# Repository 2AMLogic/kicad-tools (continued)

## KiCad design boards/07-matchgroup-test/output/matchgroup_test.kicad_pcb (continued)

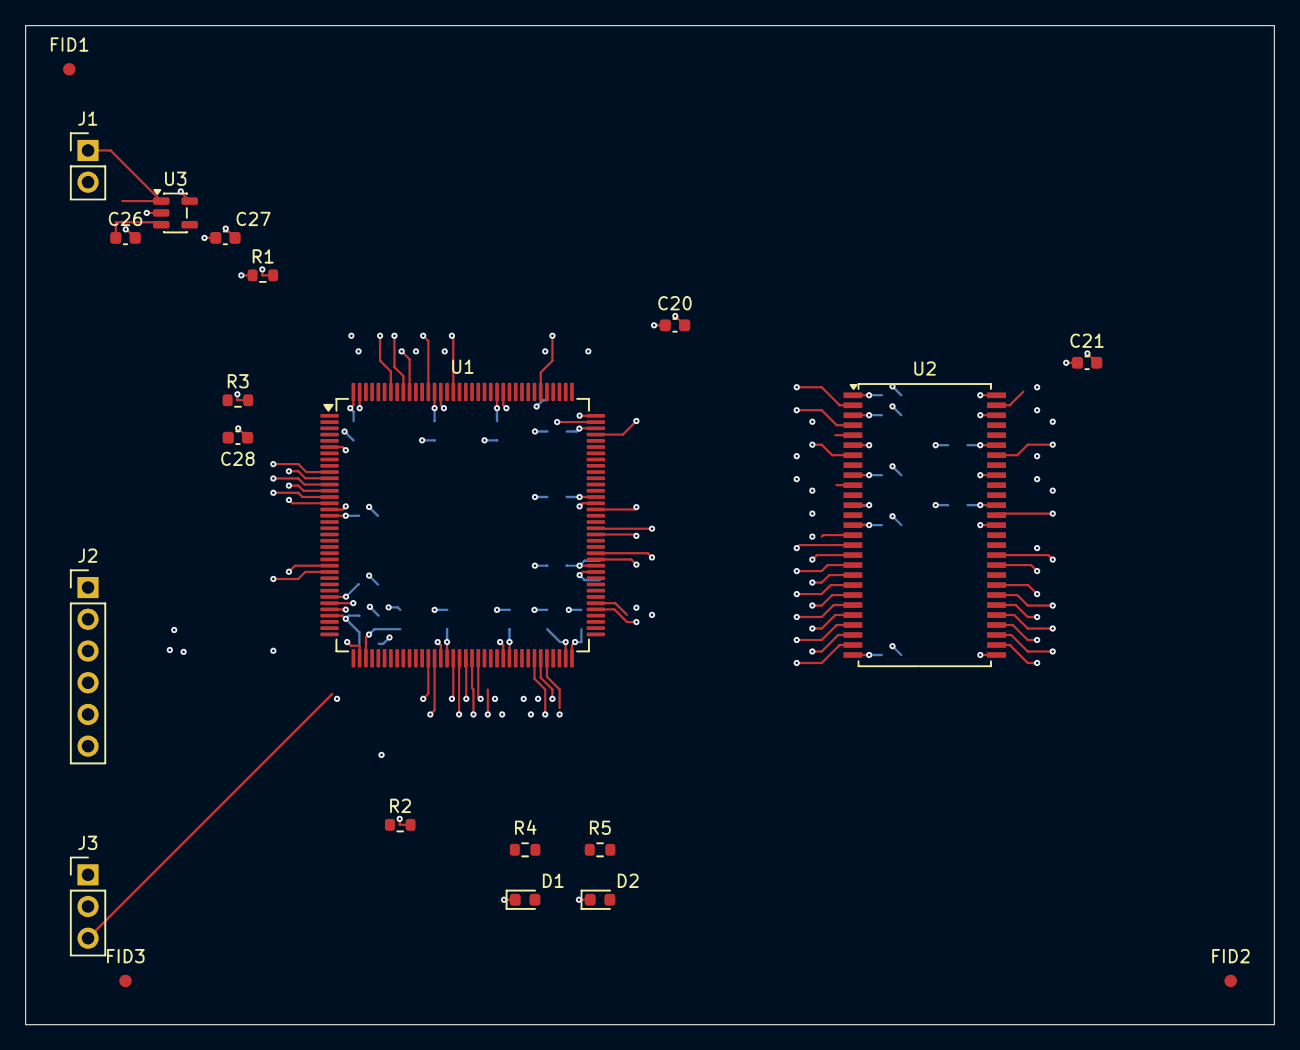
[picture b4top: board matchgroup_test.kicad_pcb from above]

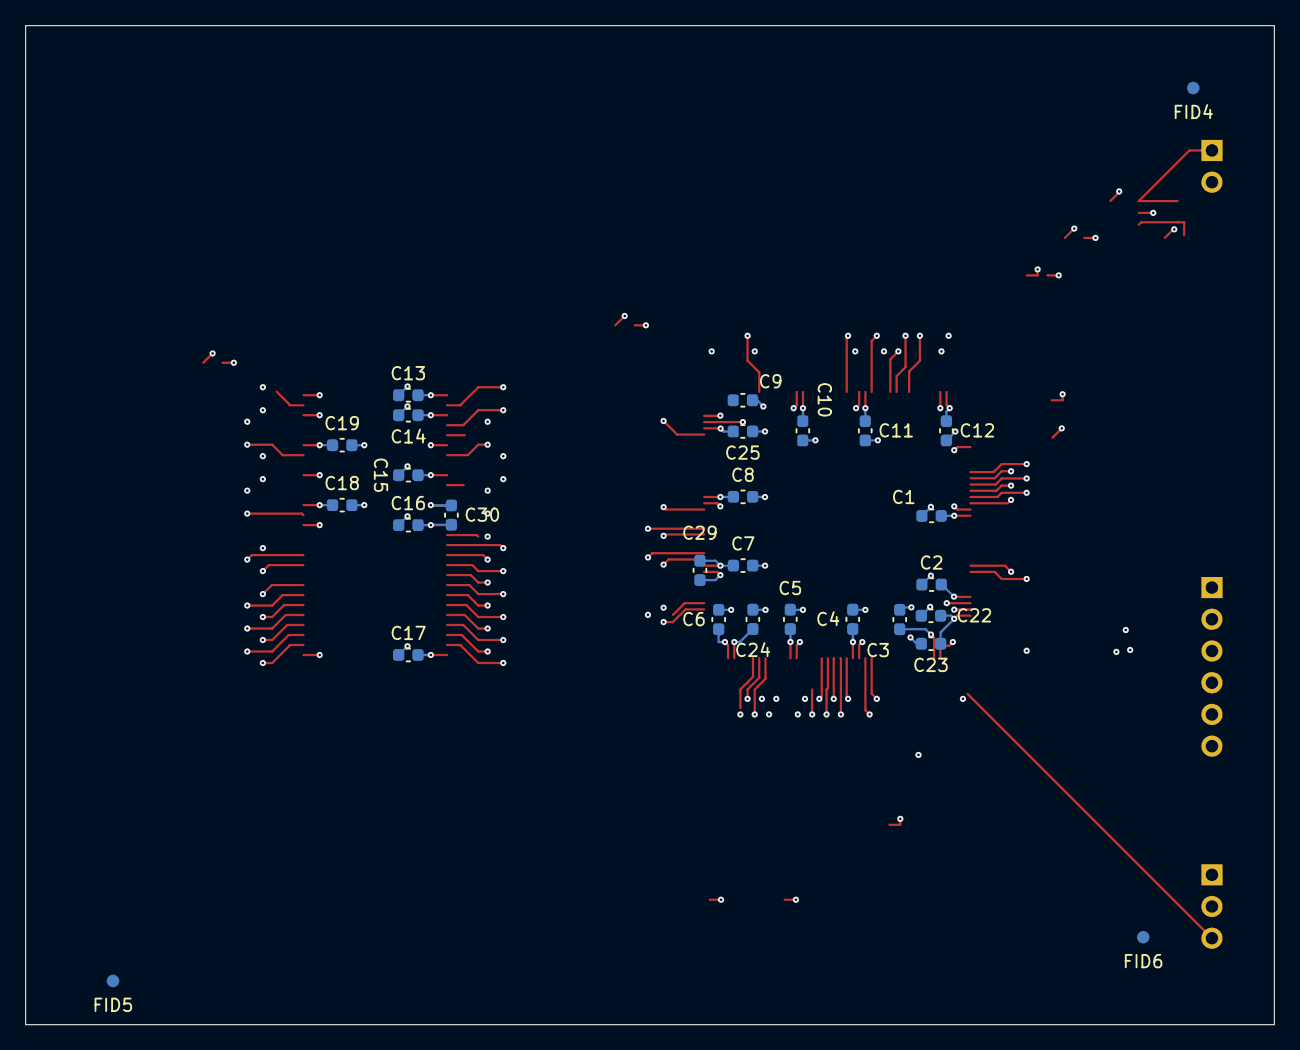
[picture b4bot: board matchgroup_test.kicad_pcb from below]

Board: 6 copper layers, 100.0 x 80.0 mm, 49 parts (28 on the bottom side), 55 nets.

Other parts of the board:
FID1, FID2, FID3, FID4, FID5, FID6: Fiducial; Fiducial_1mm_Mask2mm

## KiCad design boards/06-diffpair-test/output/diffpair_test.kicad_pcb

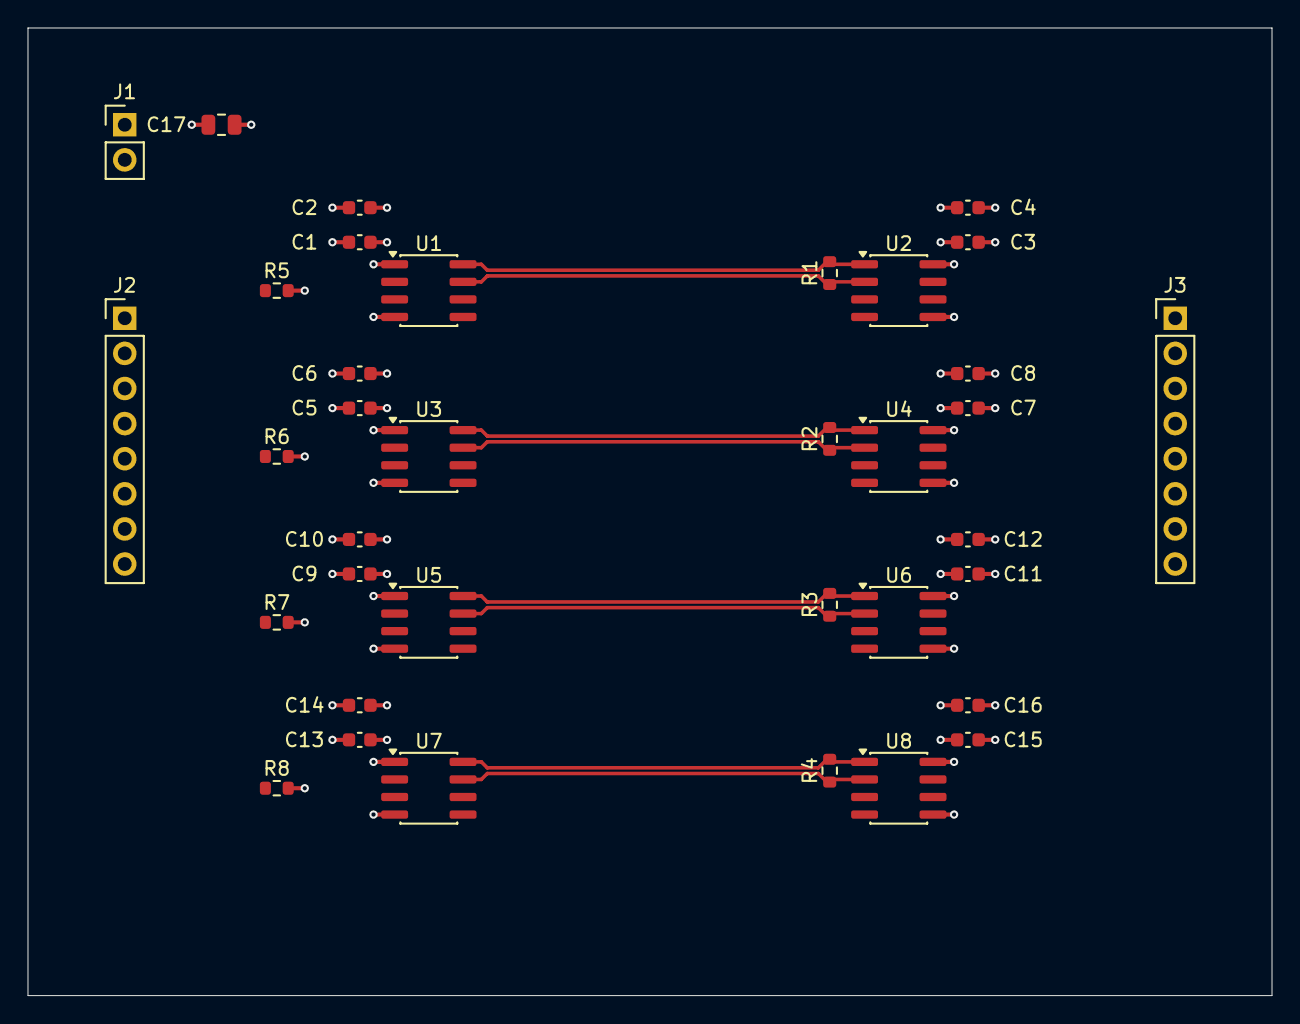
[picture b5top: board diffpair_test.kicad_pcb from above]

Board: 4 copper layers, 90.0 x 70.0 mm, 36 parts (0 on the bottom side), 18 nets.

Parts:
C1, C3, C5, C7, C9, C11, C13, C15: 1nF; C_0603_1608Metric
C2, C4, C6, C8, C10, C12, C14, C16: 100nF; C_0603_1608Metric
C17: 10uF; C_0805_2012Metric
J1: 3.3V regulated input; PinHeader_1x02_P2.54mm_Vertical
J2: IN1-4 / GND; PinHeader_1x08_P2.54mm_Vertical
J3: OUT1-4 / GND; PinHeader_1x08_P2.54mm_Vertical
R1, R2, R3, R4: 100; R_0603_1608Metric
R5, R6, R7, R8: 100k; R_0603_1608Metric
U1, U3, U5, U7: SN65LVDS1DR; SOIC-8_3.9x4.9mm_P1.27mm
U2, U4, U6, U8: SN65LVDS2DR; SOIC-8_3.9x4.9mm_P1.27mm

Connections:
+3V3: C1.1, C2.1, C3.1, C4.1, C5.1, C6.1, C7.1, C8.1, C9.1, C10.1, C11.1, C12.1, C13.1, C14.1, C15.1, C16.1, C17.1, J1.1, U1.1 (VCC), U2.8 (VCC), U3.1 (VCC), U4.8 (VCC), U5.1 (VCC), U6.8 (VCC), U7.1 (VCC), U8.8 (VCC)
GND: C1.2, C2.2, C3.2, C4.2, C5.2, C6.2, C7.2, C8.2, C9.2, C10.2, C11.2, C12.2, C13.2, C14.2, C15.2, C16.2, C17.2, J1.2, J2.2, J2.4, J2.6, J2.8, J3.2, J3.4, J3.6, J3.8, R5.2, R6.2, R7.2, R8.2, U1.4 (GND), U2.5 (GND), U3.4 (GND), U4.5 (GND), U5.4 (GND), U6.5 (GND), U7.4 (GND), U8.5 (GND)
IN1: J2.1, R5.1, U1.2 (D)
IN2: J2.3, R6.1, U3.2 (D)
IN3: J2.5, R7.1, U5.2 (D)
IN4: J2.7, R8.1, U7.2 (D)
LVDS1_N: R1.2, U1.8 (Z), U2.1 (B)
LVDS1_P: R1.1, U1.7 (Y), U2.2 (A)
LVDS2_N: R2.2, U3.8 (Z), U4.1 (B)
LVDS2_P: R2.1, U3.7 (Y), U4.2 (A)
LVDS3_N: R3.2, U5.8 (Z), U6.1 (B)
LVDS3_P: R3.1, U5.7 (Y), U6.2 (A)
LVDS4_N: R4.2, U7.8 (Z), U8.1 (B)
LVDS4_P: R4.1, U7.7 (Y), U8.2 (A)
OUT1: J3.1, U2.7 (R)
OUT2: J3.3, U4.7 (R)
OUT3: J3.5, U6.7 (R)
OUT4: J3.7, U8.7 (R)

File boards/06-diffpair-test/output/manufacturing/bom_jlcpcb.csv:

Comment,Designator,Footprint,LCSC Part #
100,"R1,R2,R3,R4",Resistor_SMD:R_0603_1608Metric,C22775
100k,"R5,R6,R7,R8",Resistor_SMD:R_0603_1608Metric,C25803
100nF,"C10,C12,C14,C16,C2,C4,C6,C8",Capacitor_SMD:C_0603_1608Metric,C14663
10uF,C17,Capacitor_SMD:C_0805_2012Metric,C15850
1nF,"C1,C11,C13,C15,C3,C5,C7,C9",Capacitor_SMD:C_0603_1608Metric,C1588
3.3V regulated input,J1,Connector_PinHeader_2.54mm:PinHeader_1x02_P2.54mm_Vertical,C492401
IN1-4 / GND; OUT1-4 / GND,"J2,J3",Connector_PinHeader_2.54mm:PinHeader_1x08_P2.54mm_Vertical,C492407
SN65LVDS1DR,"U1,U3,U5,U7",Package_SO:SOIC-8_3.9x4.9mm_P1.27mm,C2671256
SN65LVDS2DR,"U2,U4,U6,U8",Package_SO:SOIC-8_3.9x4.9mm_P1.27mm,C2671054

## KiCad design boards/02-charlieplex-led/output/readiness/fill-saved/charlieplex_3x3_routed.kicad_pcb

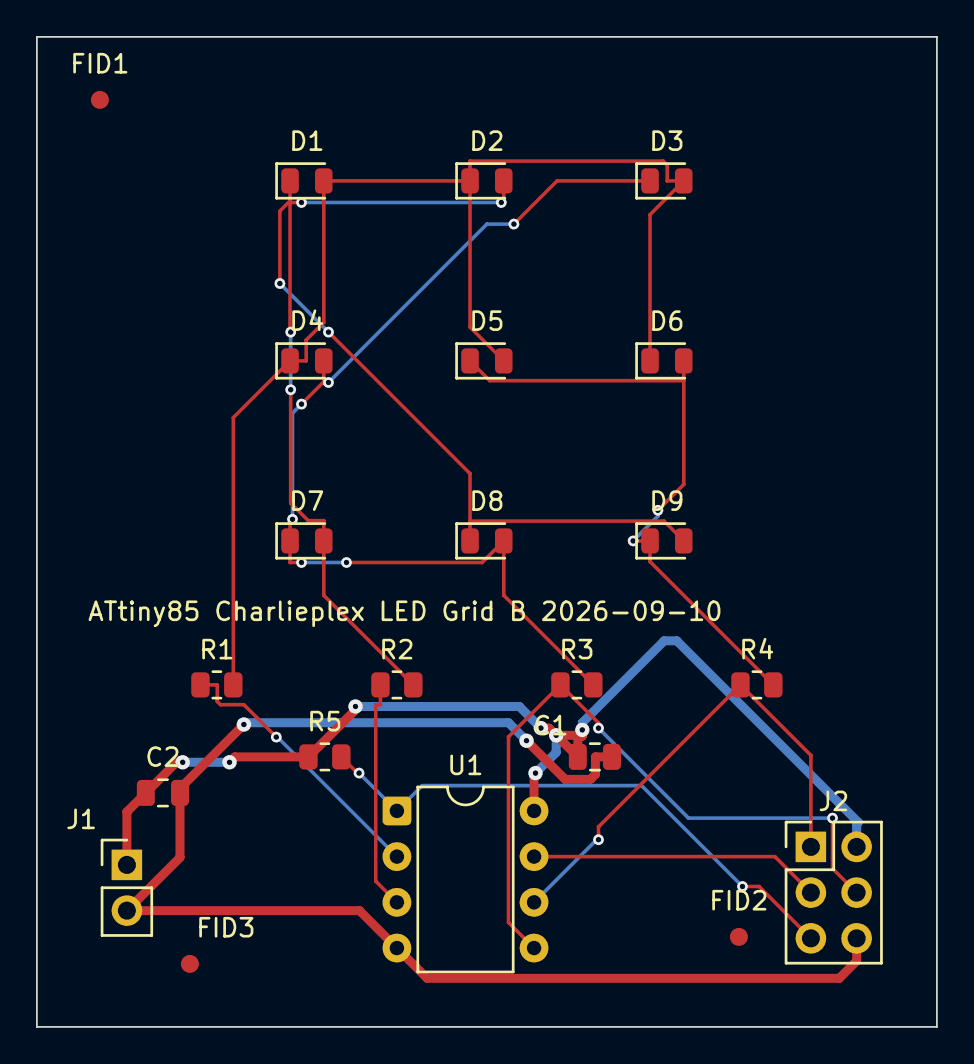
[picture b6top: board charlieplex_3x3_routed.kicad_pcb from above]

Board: 2 copper layers, 50.0 x 55.0 mm, 22 parts (0 on the bottom side), 12 nets.

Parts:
C1: 100nF; C_0805_2012Metric
C2: 4.7uF; C_0805_2012Metric
D1, D2, D3, D4, D5, D6, D7, D8, D9: LED; LED_0805_2012Metric
FID1, FID2, FID3: Fiducial; Fiducial_1mm_Mask2mm
J1: POWER; PinHeader_1x02_P2.54mm_Vertical
J2: AVR-ISP; PinHeader_2x03_P2.54mm_Vertical
R1, R2, R3, R4: 330R; R_0805_2012Metric
R5: 10k; R_0805_2012Metric
U1: ATtiny85-20PU; DIP-8_W7.62mm

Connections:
GND: C1.2, C2.2, J1.2, J2.6, U1.4 (GND)
ISP_SCK: J2.3, U1.7 (PB2)
LINE_A: R1.1, U1.2 (XTAL1/PB3)
LINE_B: R2.1, U1.3 (XTAL2/PB4)
LINE_C: J2.4, R3.1, U1.5 (AREF/PB0)
LINE_D: J2.1, R4.1, U1.6 (PB1)
NODE_A: D1.2 (A), D2.1 (K), D3.2 (A), D4.1 (K), D5.2 (A), D6.1 (K), R1.2
NODE_B: D1.1 (K), D2.2 (A), D7.2 (A), D8.1 (K), D9.2 (A), R2.2
NODE_C: D3.1 (K), D4.2 (A), D7.1 (K), D8.2 (A), R3.2
NODE_D: D5.1 (K), D6.2 (A), D9.1 (K), R4.2
RESET: J2.5, R5.2, U1.1 (~RESET/PB5)
VCC: C1.1, C2.1, J1.1, J2.2, R5.1, U1.8 (VCC)

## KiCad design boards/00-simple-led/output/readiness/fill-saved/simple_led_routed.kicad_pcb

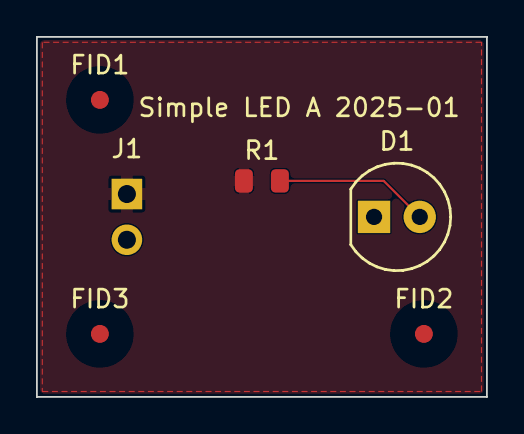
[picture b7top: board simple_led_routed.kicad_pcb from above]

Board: 2 copper layers, 25.0 x 20.0 mm, 6 parts (0 on the bottom side), 3 nets.

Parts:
D1: LED; LED_D5.0mm
FID1, FID2, FID3: Fiducial; Fiducial_1mm_Mask2mm
J1: PWR; PinHeader_1x02_P2.54mm_Vertical
R1: 330; R_0805_2012Metric

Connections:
GND: D1.1 (K), J1.2
LED_ANODE: D1.2 (A), R1.2
VCC: J1.1, R1.1

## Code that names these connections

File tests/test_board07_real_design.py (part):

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        "clock_relative_tolerance_mm": 10,
        "max_trace_length_mm": 120,
    }
    errors = validate.timing_errors({"DQ0": 50, "DQ1": 52, "SDCLK": 30, "SDNWE": 31}, constraints)
    assert len(errors) == 2
    assert all("clock-relative" in error for error in errors)
    assert (
        validate.timing_errors({"DQ0": 35, "DQ1": 37, "SDCLK": 30, "SDNWE": 31}, constraints) == []
    )


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        "clock_relative_tolerance_mm": 10,
        "max_trace_length_mm": 120,
    }
    assert validate.timing_errors({"DQ0": 20}, constraints) == ["Missing routed length: SDCLK"]


def test_inner_layer_transition_does_not_count_unused_through_barrel_as_series_length():
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    parts = {part.ref: part for part in generate.build_parts()}
    # ISSI's chip select, clock enable and byte masks must reach the correct
    # FMC bank2 pins; wrong bank1 wiring cannot be rescued by length matching.
    assert parts["U2"].pins["19"] == "SDNE1"
    assert parts["U2"].pins["37"] == "SDCKE1"
    assert parts["U2"].pins["15"] == "LDQM"
    assert parts["U2"].pins["39"] == "UDQM"
    assert "36" not in parts["U2"].pins and "40" not in parts["U2"].pins
    for pin, name in (("71", "VCAP1"), ("106", "VCAP2")):
        assert parts["U1"].pins[pin] == name
        attached = [p for p in parts.values() if name in p.pins.values()]
        assert len(attached) == 2
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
